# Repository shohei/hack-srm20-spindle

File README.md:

## About

This repository is for sharing information of hacking SRM-20 CNC spindle.

## Example parameters

- Roughing

| Content       | Value        |
| ------------- |:------------:|
| XY speed      | 5 [mm/s]     |
| Cutting depth | 0.1[mm/s]    |
| Milling tool  | 3mm Straight |

- Finishing

| Content       | Value        |
| ------------- |:------------:|
| XY speed      | 5 [mm/s]     |
| Cutting depth | 0.1[mm/s]    |
| Milling tool  | 0.5mm Ball   |

## Author
Shohei Aoki \<shoaok@gmail.com\>

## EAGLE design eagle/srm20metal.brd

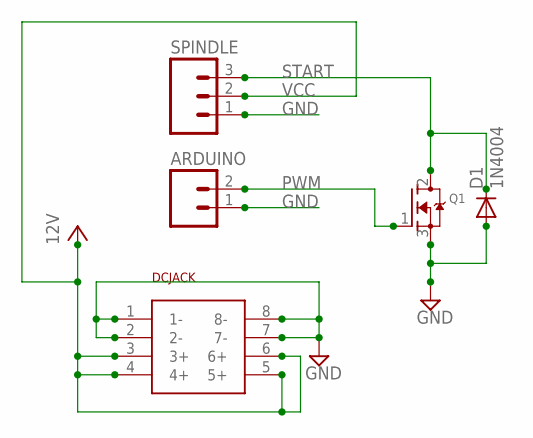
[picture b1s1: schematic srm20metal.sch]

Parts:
ARDUINO: M02PTH; 1X02
D1: 1N4004; DO41-10
Q1: MOSFET-NGDS_TO220V; TO220V
SPINDLE: M03PTH; 1X03
U$1: DCJACK; DIPKIT

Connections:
GND: ARDUINO.1, D1.A, Q1.3 (S), SPINDLE.1, U$1.1 (1-), U$1.2 (2-), U$1.7 (7-), U$1.8 (8-)
PWM: ARDUINO.2, Q1.1 (G)
START: D1.C, Q1.2 (D), SPINDLE.3
VCC: SPINDLE.2, U$1.3 (3+), U$1.4 (4+), U$1.5 (5+), U$1.6 (6+)

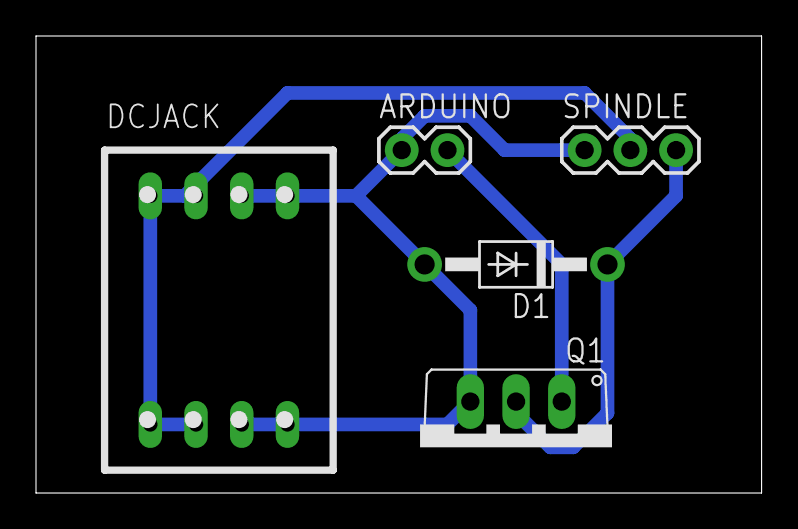
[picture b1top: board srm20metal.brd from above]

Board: 2 copper layers, 40.3 x 25.4 mm, 5 parts (0 on the bottom side), 4 nets.

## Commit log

2015-08-04 add some data
2015-08-04 add readme in arduino
2015-08-04 add about and author in readme
2015-08-04 fix typo
2015-08-04 add image
2015-08-04 add parameter in readme
2015-08-07 add drawings
2015-08-07 fix word
2015-08-29 add wiring diagram
2015-08-29 Add a sketch
2016-02-12 add eagle files

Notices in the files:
parts and their libraries:
SparkFun: Licensing: CC v3.0 Share-Alike You are welcome to use this library for commercial purposes.
